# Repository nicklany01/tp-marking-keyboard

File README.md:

# TP Marking Keyboard
## Releases
The built program can be found in github actions under the corresponding commit. There will be a file called "fireware.zip" that can be downloaded and flashed to the keyboard.
## Flashing Instructions
1. Connect the keyboard via a USB cable.
2. Double click the reset button on the keyboard (found below the rotary encoder) to enter bootloader mode. The keyboard should show up as a mass storage device on your computer.
3. Copy the "firmware.uf2" file from the downloaded release to the mass storage device to flash the keyboard. The storage device should automatically eject and the keyboard will reboot with the new firmware.
## Local Build Instructions
Source code is built in github actions using the ZMK firmware framework. To build the firmware locally, follow these steps:
1. Clone the ZMK repository using the following command:
```
git clone https://github.com/zmkfirmware/zmk.git
```
2. Set up the Zephyr SDK as described [here](https://docs.zephyrproject.org/3.5.0/develop/getting_started/index.html)
3. From the zmk directory, run the following commands to build the firwmare, ensuring to replace "/path/to/this/repo/config" with the path to the config directory in this repository:
```
cd app
west build -p -b nice_nano_v2 -- -DSHIELD=tp_marking_keyboard -DZMK_CONFIG=/path/to/this/repo/config
```
The built firmware file can be found at "/path/to/zmk/app/build/zephyr/zmk.uf2", and can be flashed with the [flash instructions](#flashing-instructions) above, treating "zmk.uf2" as "firmware.uf2".
For more information, see the [ZMK documentation](https://zmk.dev/docs/development/local-toolchain/setup/native) and [Zephyr documentation](https://docs.zephyrproject.org/3.5.0/develop/getting_started/index.html)

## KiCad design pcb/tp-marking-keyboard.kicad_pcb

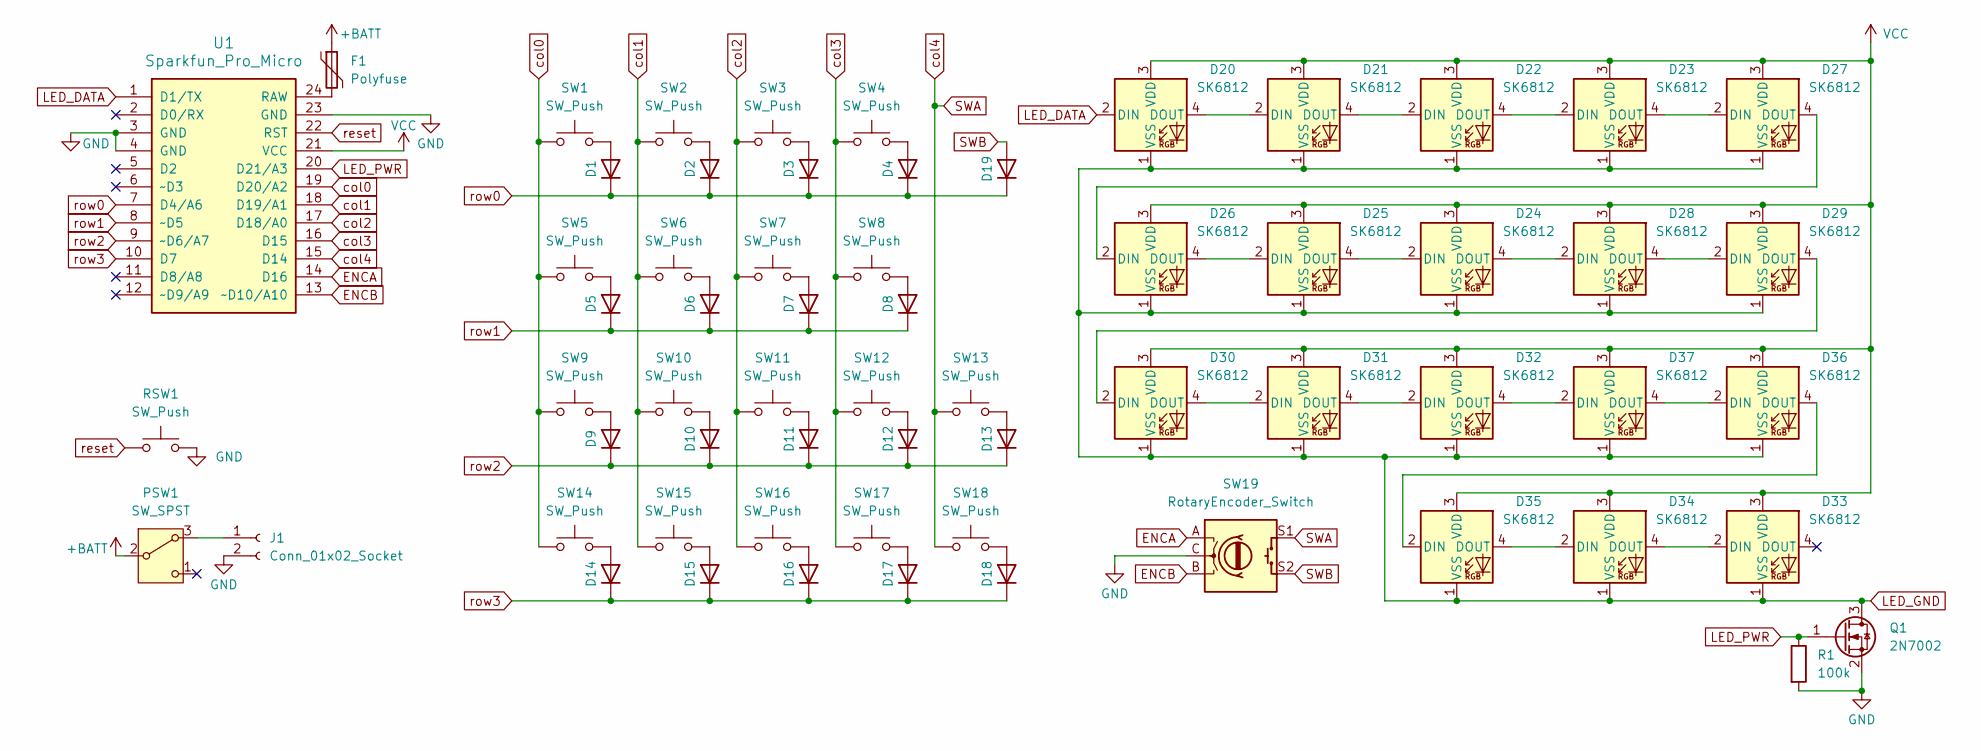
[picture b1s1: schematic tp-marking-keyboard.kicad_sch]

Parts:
D1, D2, D3, D4, D5, D6, D7, D8, D9, D10, D11, D12, D13, D14, D15, D16, D17, D18, D19: 1N4148WT; D_SOD-523
D20, D21, D22, D23, D24, D25, D26, D27, D28, D29, D30, D31, D32, D33, D34, D35, D36, D37: SK6812; SK6812_4020_SIDE_rev2
F1: Polyfuse; 0805_2012_nonpolarised
J1: Conn_01x02_Socket; JST_PH_S2B-PH-SM4-TB_1x02-1MP_P2.00mm_Horizontal
PSW1: SW_SPST; SW_SPDT_PCM12
Q1: 2N7002; SOT-23-3
R1: 100k; 0805_2012_nonpolarised
RSW1: SW_Push; SW_SPST_FSMSM
SW1, SW2, SW3, SW4, SW5, SW6, SW7, SW8, SW9, SW10, SW11, SW12, SW13, SW14, SW15, SW16, SW17, SW18: SW_Push; gateron-ks27-hotswap-reversible
SW19: RotaryEncoder_Switch; RotaryEncoder_Alps_EC11E-Switch_Vertical_H20mm
U1: Sparkfun_Pro_Micro

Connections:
+BATT: F1.1, PSW1.2 (B)
CS: U1.2 (D0/RX)
ENCA: SW19.A, U1.14 (D16)
ENCB: SW19.B, U1.13 (~D10/A10)
GND: J1.2, Q1.2 (S), R1.2, RSW1.2, SW19.C, U1.3 (GND), U1.4 (GND), U1.23 (GND)
LED_DATA: D20.2 (DIN), U1.1 (D1/TX)
LED_GND: D20.1 (VSS), D21.1 (VSS), D22.1 (VSS), D23.1 (VSS), D24.1 (VSS), D25.1 (VSS), D26.1 (VSS), D27.1 (VSS), D28.1 (VSS), D29.1 (VSS), D30.1 (VSS), D31.1 (VSS), D32.1 (VSS), D33.1 (VSS), D34.1 (VSS), D35.1 (VSS), D36.1 (VSS), D37.1 (VSS), Q1.3 (D)
LED_PWR: Q1.1 (G), R1.1, U1.20 (D21/A3)
unnamed: D1.2 (A), SW1.2
unnamed: D2.2 (A), SW2.2
unnamed: D3.2 (A), SW3.2
unnamed: D4.2 (A), SW4.2
unnamed: D5.2 (A), SW5.2
unnamed: D6.2 (A), SW6.2
unnamed: D7.2 (A), SW7.2
unnamed: D8.2 (A), SW8.2
unnamed: D9.2 (A), SW9.2
unnamed: D10.2 (A), SW10.2
unnamed: D11.2 (A), SW11.2
unnamed: D12.2 (A), SW12.2
unnamed: D13.2 (A), SW13.2
unnamed: D14.2 (A), SW14.2
unnamed: D15.2 (A), SW15.2
unnamed: D16.2 (A), SW16.2
unnamed: D17.2 (A), SW17.2
unnamed: D18.2 (A), SW18.2
unnamed: D20.4 (DOUT), D21.2 (DIN)
unnamed: D21.4 (DOUT), D22.2 (DIN)
unnamed: D22.4 (DOUT), D23.2 (DIN)
unnamed: D23.4 (DOUT), D27.2 (DIN)
unnamed: D24.2 (DIN), D25.4 (DOUT)
unnamed: D24.4 (DOUT), D28.2 (DIN)
unnamed: D25.2 (DIN), D26.4 (DOUT)
unnamed: D26.2 (DIN), D27.4 (DOUT)
unnamed: D28.4 (DOUT), D29.2 (DIN)
unnamed: D29.4 (DOUT), D30.2 (DIN)
unnamed: D30.4 (DOUT), D31.2 (DIN)
unnamed: D31.4 (DOUT), D32.2 (DIN)
unnamed: D32.4 (DOUT), D37.2 (DIN)
unnamed: D33.2 (DIN), D34.4 (DOUT)
unnamed: D34.2 (DIN), D35.4 (DOUT)
unnamed: D35.2 (DIN), D36.4 (DOUT)
unnamed: D36.2 (DIN), D37.4 (DOUT)
unnamed: J1.1, PSW1.3 (A)
unnamed: F1.2, U1.24 (RAW)
SWA: SW13.1, SW18.1, SW19.S1, U1.15 (D14)
SWB: D19.2 (A), SW19.S2
VCC: D20.3 (VDD), D21.3 (VDD), D22.3 (VDD), D23.3 (VDD), D24.3 (VDD), D25.3 (VDD), D26.3 (VDD), D27.3 (VDD), D28.3 (VDD), D29.3 (VDD), D30.3 (VDD), D31.3 (VDD), D32.3 (VDD), D33.3 (VDD), D34.3 (VDD), D35.3 (VDD), D36.3 (VDD), D37.3 (VDD), U1.21 (VCC)
col0: SW1.1, SW5.1, SW9.1, SW14.1, U1.19 (D20/A2)
col1: SW2.1, SW6.1, SW10.1, SW15.1, U1.18 (D19/A1)
col2: SW3.1, SW7.1, SW11.1, SW16.1, U1.17 (D18/A0)
col3: SW4.1, SW8.1, SW12.1, SW17.1, U1.16 (D15)
reset: RSW1.1, U1.22 (RST)
row0: D1.1 (K), D2.1 (K), D3.1 (K), D4.1 (K), D19.1 (K), U1.7 (D4/A6)
row1: D5.1 (K), D6.1 (K), D7.1 (K), D8.1 (K), U1.8 (~D5)
row2: D9.1 (K), D10.1 (K), D11.1 (K), D12.1 (K), D13.1 (K), U1.9 (~D6/A7)
row3: D14.1 (K), D15.1 (K), D16.1 (K), D17.1 (K), D18.1 (K), U1.10 (D7)

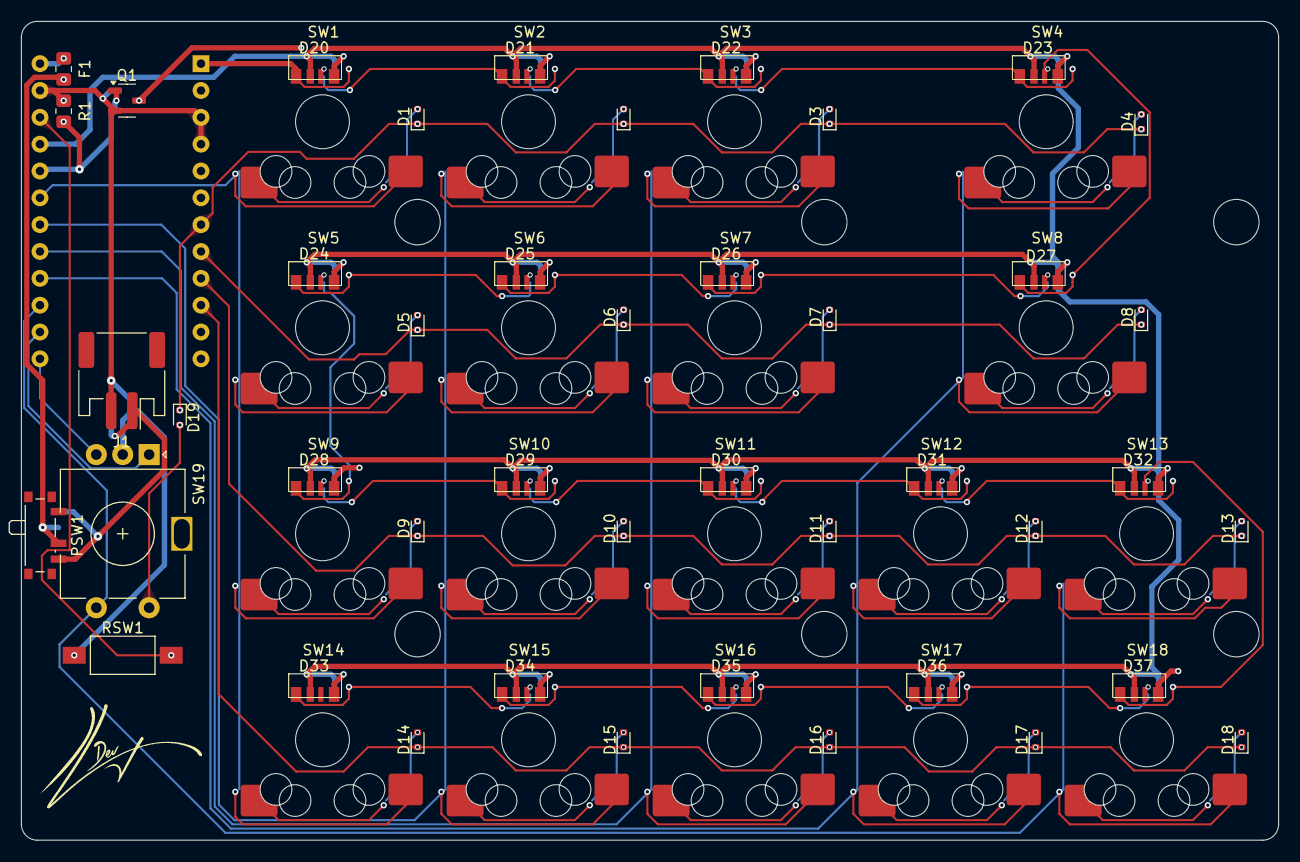
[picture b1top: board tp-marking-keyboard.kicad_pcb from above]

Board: 2 copper layers, 119.0 x 77.5 mm, 63 parts (1 on the bottom side), 56 nets.

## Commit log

2025-10-28 Initial User Config.
2025-10-28 Add PCB design
2025-10-28 Move led footprints lower
2025-10-28 Add board overlay
2025-10-28 Add build and flash documentation
2025-10-28 Add additional layers, and pass/fail macro
2025-10-28 Add led underglow foundations
2025-10-30 Add layer for markers
2025-10-30 Add rotary encoder
2025-10-30 Ajust rotary encoder rotation increments
